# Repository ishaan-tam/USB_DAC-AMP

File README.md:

# Pocket USB DAC Headphone Amp

# USB DAC + Baxandall Tone Control Headphone Amp  
**Checklist / Build Plan**

make sure that resistors are thin film, thich film resistors can introduce distortion
Chose electrolytic caps in the signal path as long as they are large enough, if chosing ceramic (sepecially in the signal path) chose type cog, otehrwise most ceramic caps will have piezoelectric effects and will introduce distortion 
bypass caps can be pretty much any type

For voltage ratings, useually go with double of what the expected DC voltage is
---

## Phase 0 — Lock the architecture
- [ ] Use **Phil’s USB headphone amplifier** as the base design
  - [ ] USB-C power + data
  - [ ] USB audio codec (PCM290x family)
  - [ ] DAC output buffer / reconstruction filter
  - [ ] Volume control stage
  - [ ] Output/current-drive stage to headphone jack
- [ ] Insert **TI Baxandall bass/treble tone control** as a line-level block
  - [ ] Signal flow:  
    **Phil DAC buffer → TI Baxandall tone → Phil volume → Phil output stage**
- [ ] Decide on **single master volume**
  - [ ] Use Phil’s volume control only
  - [ ] Bypass TI’s R1/R2 volume pots

---

## Phase 1 — KiCad schematic integration
- [ ] Create a **combined KiCad schematic**
  - [ ] Start from Phil’s schematic as the backbone
  - [ ] Add TI Baxandall tone block between Phil buffer output and Phil volume input
  - [ ] Keep TI input buffers initially (lower risk)
- [ ] **Bypass TI R1/R2 (volume pots)**
  - [ ] Remove R1/R2 from the TI tone schematic
  - [ ] Feed TI input buffer directly from the coupling cap
  - [ ] Add a DC bias path so the node does not float
  - [ ] (Optional) Add footprints / jumpers to re-enable pots if needed
- [ ] **Resolve virtual ground vs real ground**
  - [ ] Identify Phil’s analog reference / bias node (half-rail if single-supply)
  - [ ] Tie all TI “mid” nodes to Phil’s analog reference
  - [ ] Do NOT generate a separate TI virtual ground if Phil already provides one
- [ ] Perform a **sanity check**
  - [ ] Verify signal levels between stages
  - [ ] Ensure tone boost will not clip internal op-amps
  - [ ] Ensure compatibility with Phil’s volume stage input impedance

---

## Phase 2 — BOM & sourcing
- [ ] Create a **BOM from the combined schematic**
  - [ ] ICs (codec, op-amps, regulators)
  - [ ] Precision resistors where required
  - [ ] Capacitors (type + voltage rating)
  - [ ] Dual-gang pots for bass/treble
  - [ ] USB-C connector, headphone jack
  - [ ] Protection parts (ESD diodes, fuses, ferrites)
- [ ] Align BOM with **JLCPCB / LCSC availability**
  - [ ] Decide which ICs are hand-soldered
  - [ ] Mark which passives are PCBA-assembled
- [ ] Order parts
  - [ ] Order extras for iteration (pots, op-amps, passives)

---

## Phase 3 — Build & test
- [ ] Bring-up in stages
  - [ ] Test Phil’s base circuit (USB enumeration + clean audio)
  - [ ] Enable TI Baxandall tone block
  - [ ] Verify flat response at center
  - [ ] Verify bass/treble behavior
- [ ] Full system test
  - [ ] Verify volume control behavior
  - [ ] Test with headphones
  - [ ] Listen for noise, clipping, oscillation

---

## Phase 4 — Rev A refinement
- [ ] Adjust Baxandall network for **subtle** tone range if needed
- [ ] Improve decoupling/layout if noise or instability appears
- [ ] Finalize schematic and prepare for PCB layout / PCBA

A compact, USB-powered headphone amplifier built around a **class-compliant USB audio codec**, with an **analog signal path**, **physical volume control**, and room to add **Baxandall bass/treble tone shaping** in later revisions.

This project prioritizes:
- **Fun, hands-on analog audio**
- **Simple, driverless USB DAC operation**
- **Incremental development** (breadboard → PCB Rev A → Rev B tone control)

Not meant to be “audiophile-perfect,” but absolutely meant to be **good enough that I actually want to use it**.

---

## Project Status

- **Current phase:** Rev 0 — Breadboard prototype
- **Goal of Rev 0:**  
  - USB device enumerates as an audio output  
  - Audio plays cleanly through headphones  
  - Volume control works  
- **Future phases:**  
  - Rev A PCB (compact, USB-C, integrated headphone stage)  
  - Rev B (add Baxandall bass/treble tone control)

---

## High-Level Architecture

USB-C
│
├─ USB 2.0 D+/D−
│
PCM2906C USB Audio Codec
│
├─ DAC L/R (line-level)
│
Buffer + Reconstruction Filter
│
(Rev B) Baxandall Tone Control (Bass / Treble)
│
Volume Control
│
Headphone Output Stage
│
3.5 mm Headphone Jack

---

## Key Design Decisions

### USB Audio Codec
- **TI PCM2906C**
  - USB Audio Class 1 (driverless)
  - Plug-and-play on **Windows, macOS, Linux**
  - Likely works on **USB-C iPhones** (with power constraints)
  - Chosen over older PCM2900 due to **availability / active status**

S/PDIF pins are **not used** in this project.

---

### Power Strategy
- **Rev 0 (breadboard):**  
  - USB 5 V only  
  - No boost converter  
- **Rev A (PCB):**  
  - USB 5 V → boost → clean analog rail (12–15 V)  
  - Boost is for **headroom**, not “audio amplification”

---

### Analog Audio Philosophy
- Keep the **DAC isolated** from headphone loads
- Use **buffers** and **volume control** before the output stage
- Tone control is **optional and playful**, not surgical EQ
- If “serious EQ” is needed → do it digitally in software

---

### Tone Control Plan
- **Baxandall bass/treble** (2 knobs)
  - Musical, forgiving
  - Simple, stable, well-understood
- Will be added in **Rev B**
- Rev A PCB should reserve insertion points for it

---

## Breadboard Prototype (Rev 0)

### What Rev 0 Includes
- PCM2906C wired per TI **Typical Application Circuit**
- 12 MHz crystal + required decoupling
- USB-C input (USB 2.0 only)
- Line-level L/R output
- External headphone amp module **or** simple buffer + volume pot
- Goal: **“I hear sound and can control volume”**

### What Rev 0 Intentionally Avoids
- Boost converters
- Parallel op-amps
- Tone controls
- EMI optimization
- Fancy layouts

Rev 0 is about **function, not polish**.

---

## Headphone Output (Rev 0 Approach)

For breadboarding, the headphone stage is intentionally simplified:

### Options
1. **External headphone amp module**
   - Accepts line-level L/R
   - Powered from 5 V
   - Drives headphones safely
2. **DIY buffer + volume + output stage**
   - Unity-gain buffer
   - Passive volume pot
   - Headphone-capable driver

Modules are preferred for Rev 0 to avoid stability issues on a breadboard.

---

## Compatibility Expectations

- **Windows:** ✅ Plug-and-play
- **macOS / Linux:** ✅ Plug-and-play
- **USB-C iPhone:** ⚠️ Likely works, power-dependent
- **Lightning iPhone:** ⚠️ Requires camera adapter

---

## Repository Structure

pocket-usb-dac-amp/
├─ README.md
├─ docs/
│ ├─ requirements.md
│ ├─ architecture.md
│ ├─ bringup-notes.md
│ └─ images/
├─ hardware/
│ ├─ rev0_breadboard/
│ │ ├─ wiring/
│ │ └─ bom/
│ │ └─ bom_rev0.xlsx
│ ├─ revA_pcb/
│ │ ├─ kicad/
│ │ ├─ outputs/
│ │ └─ bom/
│ └─ revB_tonecontrol/
├─ tools/
│ └─ bom/
└─ CHANGELOG.md

---

## BOM Management

- BOMs are maintained in **Excel**
- Each revision has its own BOM:
  - `bom_rev0.xlsx`
  - `bom_revA.xlsx`
- BOM includes:
  - Manufacturer + MPN
  - Supplier + SKU
  - Unit cost
  - Alternates
  - Notes (DNP, experimental, etc.)

KiCad-exported CSVs are treated as **derived artifacts**, not the source of truth.

---

## Development Philosophy

- Build **one working version at a time**
- Breadboard first, PCB later
- Prefer **known-good reference circuits**
- Avoid “clever” designs that increase debug time
- Leave room for iteration and learning

---

## Non-Goals (Important)

- Not chasing ultra-low THD numbers
- Not competing with commercial DACs
- Not building a DSP playground
- Not optimizing for mass production

This is a **learning + enjoyment project**, not a product launch.

---

## Next Immediate Steps

1. Finish Rev 0 breadboard wiring
2. Confirm USB enumeration + audio playback
3. Document bring-up issues and fixes
4. Decide:
   - integrated output stage vs module
5. Begin Rev A schematic capture

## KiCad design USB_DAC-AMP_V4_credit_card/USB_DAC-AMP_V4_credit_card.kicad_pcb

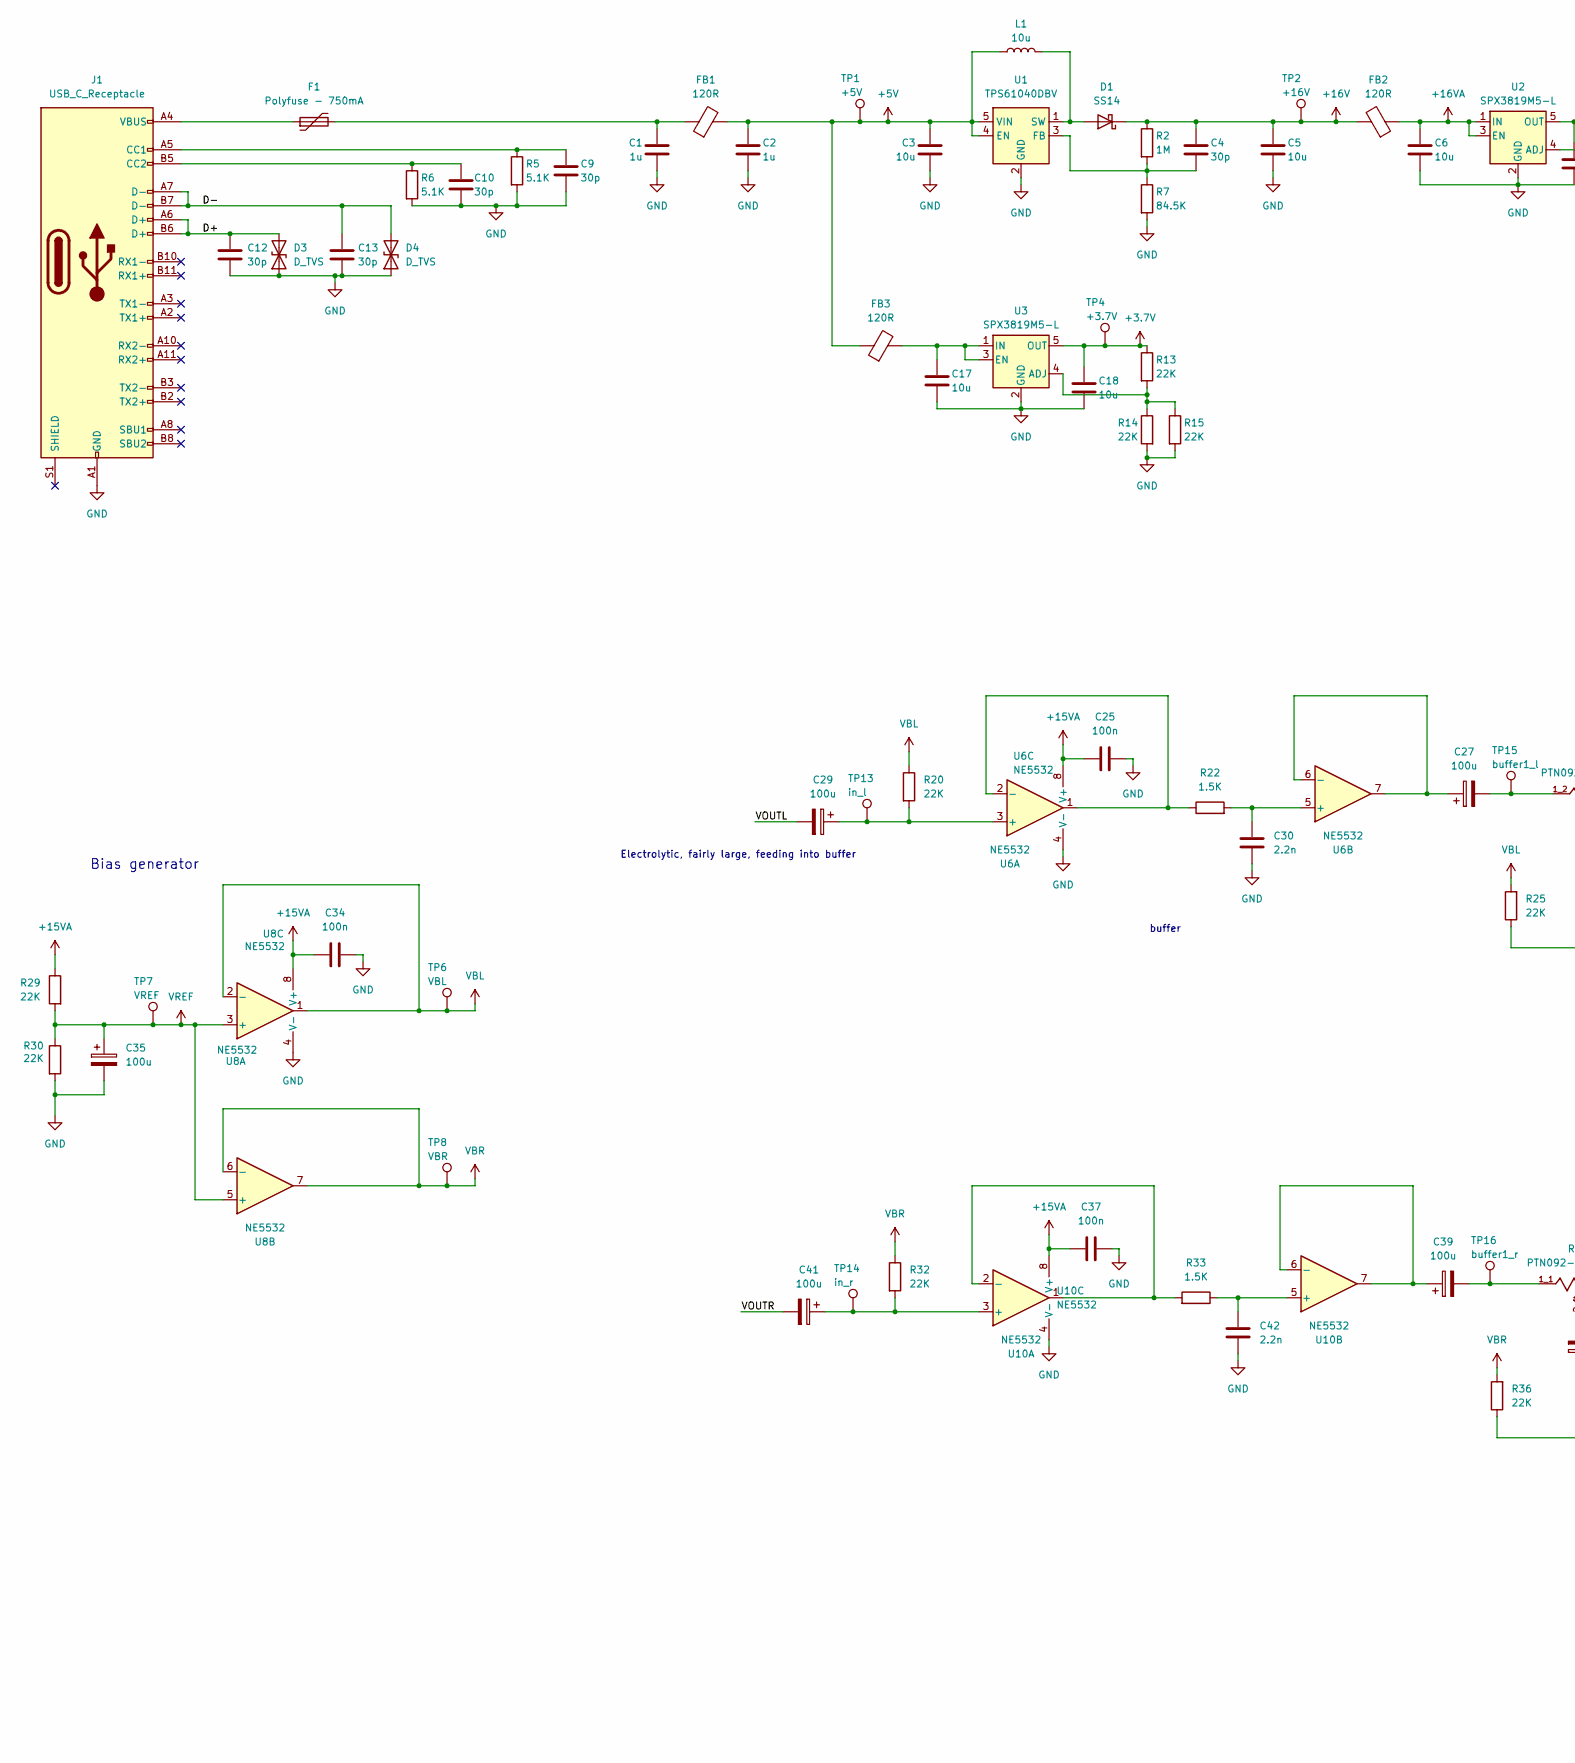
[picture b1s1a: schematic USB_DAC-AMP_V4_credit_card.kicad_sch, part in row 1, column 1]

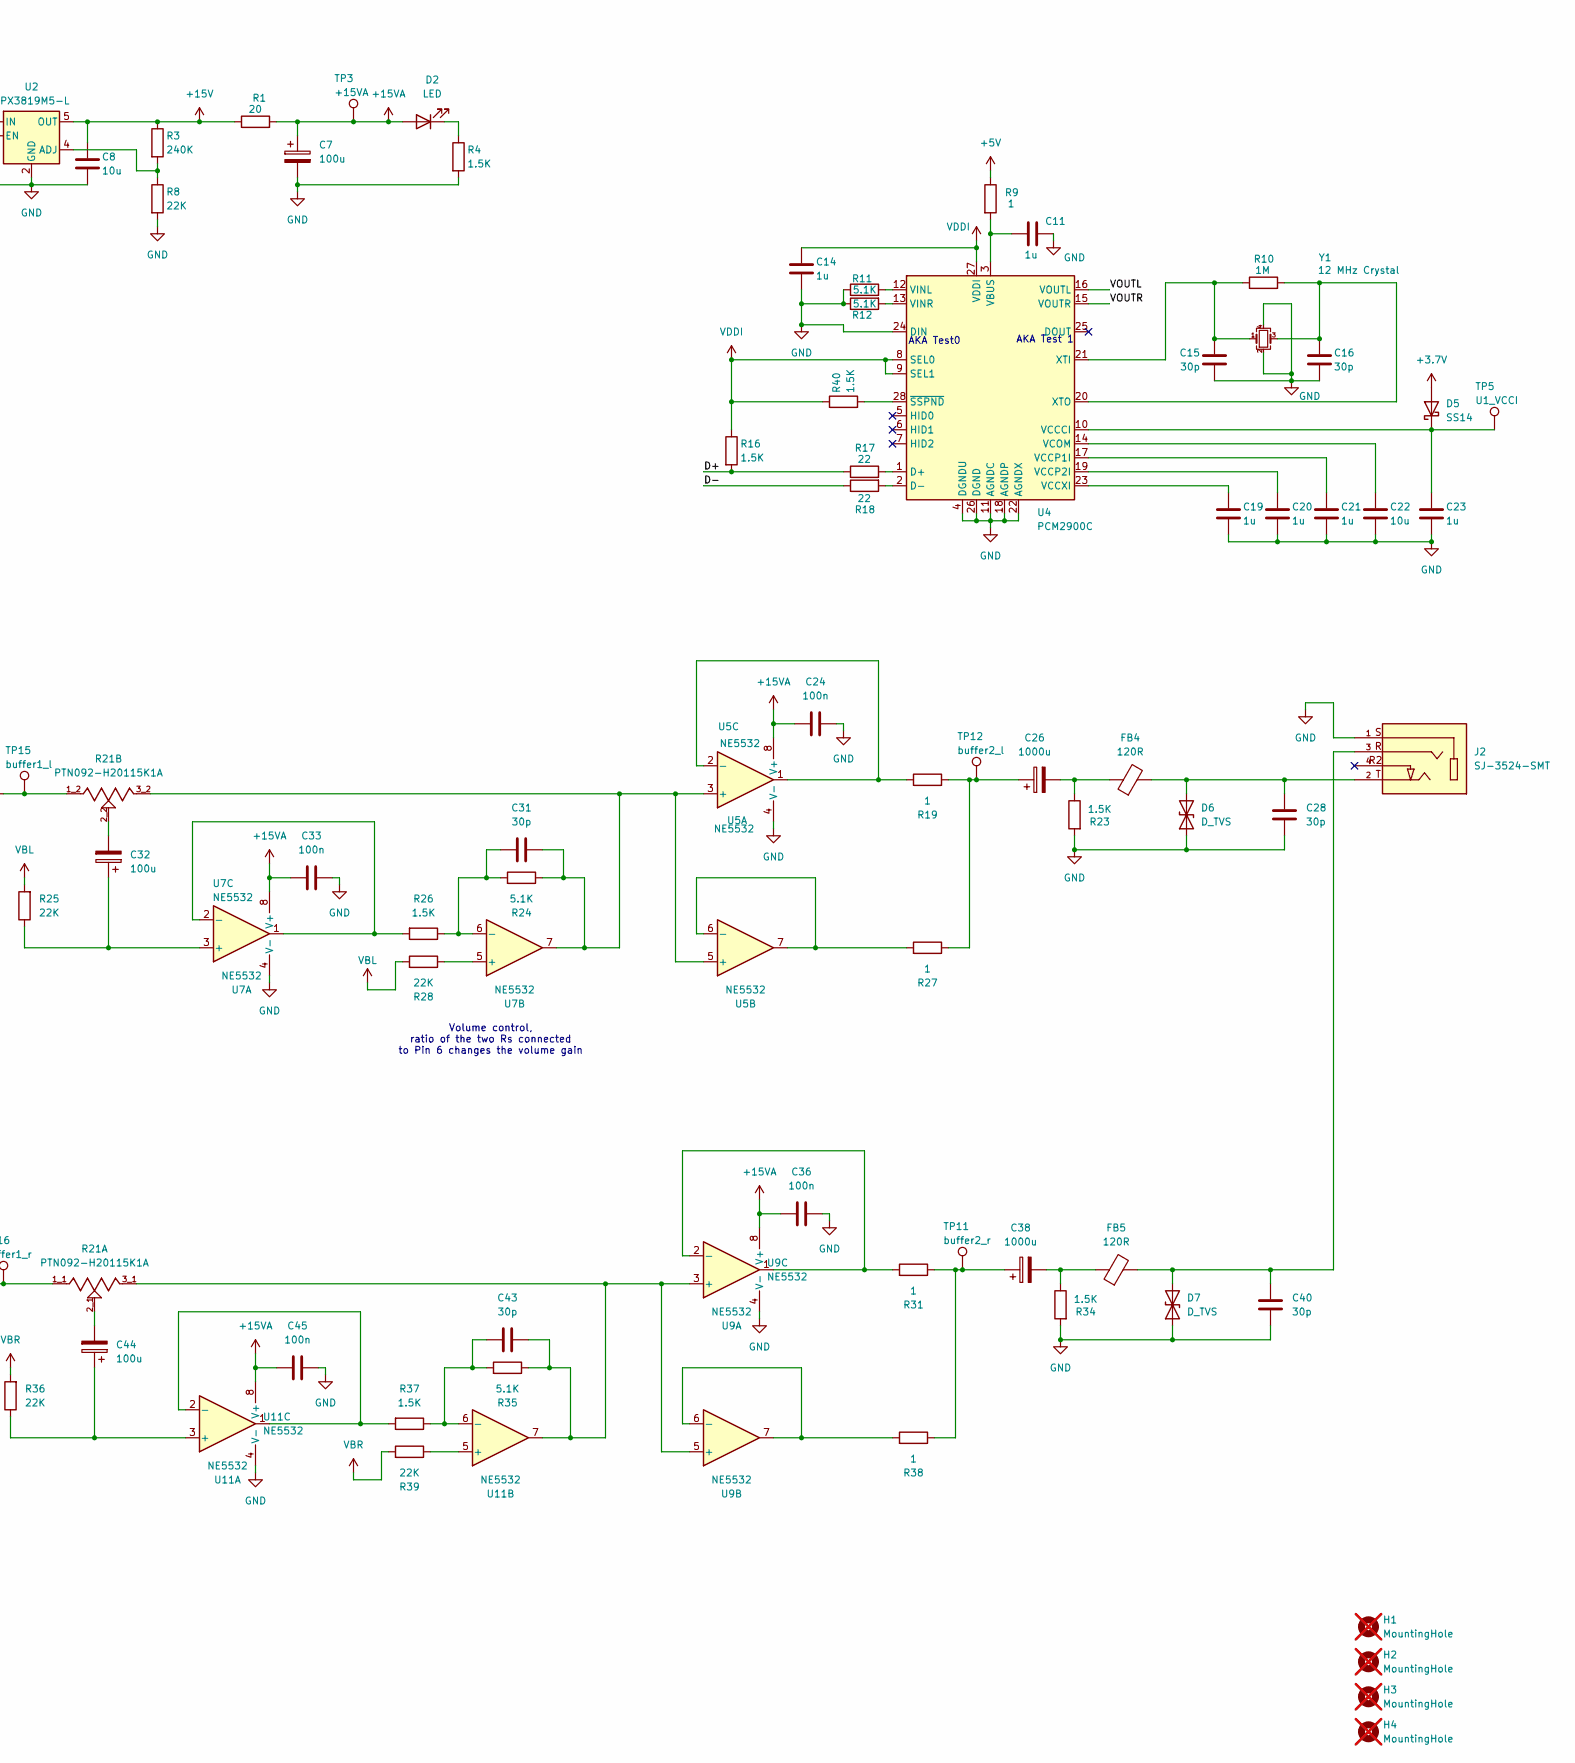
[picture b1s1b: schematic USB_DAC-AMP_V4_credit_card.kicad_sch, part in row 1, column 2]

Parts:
C1, C2, C11, C14, C19, C20, C21, C23: 1u; C_0603_1608Metric; LCSC C1592
C3, C5, C6, C8, C17, C18, C22: 10u; C_0603_1608Metric; LCSC C1035
C4, C9, C10, C12, C13, C15, C16, C28, C31, C40, C43: 30p; C_0603_1608Metric; LCSC C1658
C7, C27, C29, C32, C35, C39, C41, C44: 100u; CP_Elec_6.3x7.7; LCSC C3339
C24, C25, C33, C34, C36, C37, C45: 100n; C_0603_1608Metric; LCSC C1590
C26, C38: 1000u; CP_Elec_10x10.5; LCSC C3359
C30, C42: 2.2n; C_0603_1608Metric; LCSC C1028
D1, D5: SS14; D_SMA; LCSC C2480
D2: LED; LED_0603_1608Metric; LCSC C84265
D3, D4, D6, D7: D_TVS; D_0603_1608Metric; LCSC C316055
F1: Polyfuse - 750mA; Fuse_0603_1608Metric; LCSC C20787
FB1, FB2, FB3, FB4, FB5: 120R; R_0603_1608Metric; LCSC C12391
H1, H2, H3, H4: MountingHole; MountingHole_3.5mm; not fitted
J1: USB_C_Receptacle; USB_C_Receptacle_GCT_USB4105-xx-A_16P_TopMnt_Horizontal; LCSC C5184243
J2: SJ-3524-SMT; PARTREV 1.03; DigiKey_Part_Number CP-3524SJCT-ND
L1: 10u; L_0805_2012Metric; LCSC C223269
R1: 20; R_0603_1608Metric; LCSC C136969
R2, R10: 1M; R_0603_1608Metric; LCSC C326730
R3: 240K; R_0603_1608Metric; LCSC C217899
R4, R16, R22, R23, R26, R33, R34, R37, R40: 1.5K; R_0603_1608Metric; LCSC C193681
R5, R6, R11, R12, R24, R35: 5.1K; R_0603_1608Metric; LCSC C122969
R7: 84.5K; R_0603_1608Metric; LCSC C705797
R8, R13, R14, R15, R20, R25, R28, R29, R30, R32, R36, R39: 22K; R_0603_1608Metric; LCSC C217885
R9, R19, R27, R31, R38: 1; R_0603_1608Metric; LCSC C412388
R17, R18: 22; R_0603_1608Metric; LCSC C217888
R21: PTN092-H20115K1A; TRIM_PTN092-H20115K1A; PARTREV 1.01; DigiKey_Part_Number 2223-PTN092-H20115K1A-ND
TP1: +5V; TestPoint_Pad_1.0x1.0mm
TP2: +16V; TestPoint_Pad_1.0x1.0mm
TP3: +15VA; TestPoint_Pad_1.0x1.0mm
TP4: +3.7V; TestPoint_Pad_1.0x1.0mm
TP5: U1_VCCI; TestPoint_Pad_1.0x1.0mm
TP6: VBL; TestPoint_Pad_1.0x1.0mm
TP7: VREF; TestPoint_Pad_1.0x1.0mm
TP8: VBR; TestPoint_Pad_1.0x1.0mm
TP11: buffer2_r; TestPoint_Pad_1.0x1.0mm
TP12: buffer2_l; TestPoint_Pad_1.0x1.0mm
TP13: in_l; TestPoint_Pad_1.0x1.0mm
TP14: in_r; TestPoint_Pad_1.0x1.0mm
TP15: buffer1_l; TestPoint_Pad_1.0x1.0mm
TP16: buffer1_r; TestPoint_Pad_1.0x1.0mm
U1: TPS61040DBV; SOT-23-5; LCSC C7722
U2, U3: SPX3819M5-L; SOT-23-5; LCSC C9056
U4: PCM2900C; SSOP-28_5.3x10.2mm_P0.65mm; LCSC C180425
U5, U6, U7, U8, U9, U10, U11: NE5532; SOIC-8_3.9x4.9mm_P1.27mm; LCSC C7426
Y1: 12 MHz Crystal; Crystal_SMD_3225-4Pin_3.2x2.5mm; LCSC C9002

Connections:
+3.7V: C18.1, D5.2 (A), R13.1, TP4.1, U3.5 (OUT)
+5V: C2.1, C3.1, FB1.2, FB3.1, L1.1, R9.1, TP1.1, U1.4 (EN), U1.5 (VIN)
+15V: C8.1, R1.1, R3.1, U2.5 (OUT)
+15VA: C7.1, C24.1, C25.1, C33.1, C34.1, C36.1, C37.1, C45.1, D2.2 (A), R1.2, R29.1, TP3.1, U5.8 (V+), U6.8 (V+), U7.8 (V+), U8.8 (V+), U9.8 (V+), U10.8 (V+), U11.8 (V+)
+16V: C4.1, C5.1, D1.1 (K), FB2.2, R2.1, TP2.1
+16VA: C6.1, FB2.1, U2.1 (IN), U2.3 (EN)
/D+: C12.1, D3.2 (A2), J1.A6 (D+), J1.B6 (D+), R16.2, R17.1
/D-: C13.1, D4.2 (A2), J1.A7 (D-), J1.B7 (D-), R18.1
/VOUTL: C29.2, U4.16 (VOUTL)
/VOUTR: C41.2, U4.15 (VOUTR)
GND: C1.2, C2.2, C3.2, C5.2, C6.2, C7.2, C8.2, C9.2, C10.2, C11.2, C12.2, C13.2, C14.2, C15.2, C16.2, C17.2, C18.2, C19.2, C20.2, C21.2, C22.2, C23.2, C24.2, C25.2, C28.1, C30.1, C33.2, C34.2, C35.2, C36.2, C37.2, C40.1, C42.1, C45.2, D3.1 (A1), D4.1 (A1), D6.1 (A1), D7.1 (A1), J1.A1 (GND), J1.A12 (GND), J1.B1 (GND), J1.B12 (GND), J2.1, R4.2, R5.2, R6.2, R7.2, R8.2, R11.1, R12.1, R14.2, R15.2, R23.2, R30.2, R34.2, U1.2 (GND), U2.2 (GND), U3.2 (GND), U4.4 (DGNDU), U4.11 (AGNDC), U4.18 (AGNDP), U4.22 (AGNDX), U4.24 (DIN), U4.26 (DGND), U5.4 (V-), U6.4 (V-), U7.4 (V-), U8.4 (V-), U9.4 (V-), U10.4 (V-), U11.4 (V-), Y1.2, Y1.4
unnamed: C1.1, F1.2, FB1.1
unnamed: C26.1, R19.2, R27.1, TP12.1
unnamed: C26.2, FB4.1, R23.1
unnamed: C27.2, R21.1_2, TP15.1
unnamed: C32.2, R21.2_2
unnamed: C38.1, R31.1, R38.1, TP11.1
unnamed: C38.2, FB5.1, R34.1
unnamed: C39.2, R21.1_1, TP16.1
unnamed: C44.2, R21.2_1
unnamed: D1.2 (A), L1.2, U1.1 (SW)
unnamed: D2.1 (K), R4.1
unnamed: C23.1, D5.1 (K), TP5.1, U4.10 (VCCCI)
unnamed: C28.2, D6.2 (A2), FB4.2, J2.2
unnamed: C40.2, D7.2 (A2), FB5.2, J2.3
unnamed: F1.1, J1.A4 (VBUS), J1.A9 (VBUS), J1.B4 (VBUS), J1.B9 (VBUS)
unnamed: C9.1, J1.A5 (CC1), R5.1
unnamed: C10.1, J1.B5 (CC2), R6.1
unnamed: C4.2, R2.2, R7.1, U1.3 (FB)
unnamed: R3.2, R8.1, U2.4 (ADJ)
unnamed: R13.2, R14.1, R15.1, U3.4 (ADJ)
unnamed: C17.1, FB3.2, U3.1 (IN), U3.3 (EN)
unnamed: R17.2, U4.1 (D+)
unnamed: R18.2, U4.2 (D-)
unnamed: C11.1, R9.2, U4.3 (VBUS)
unnamed: C21.1, U4.17 (VCCP1I)
unnamed: C20.1, U4.19 (VCCP2I)
unnamed: C19.1, U4.23 (VCCXI)
unnamed: C22.1, U4.14 (VCOM)
unnamed: R11.2, U4.12 (VINL)
unnamed: R12.2, U4.13 (VINR)
unnamed: C15.1, R10.1, U4.21 (XTI), Y1.1
unnamed: C16.1, R10.2, U4.20 (XTO), Y1.3
unnamed: R40.2, U4.28 (~SSPND)
unnamed: C31.2, R21.3_2, R24.1, U5.3 (+), U5.5 (+), U7.7
unnamed: R19.1, U5.1, U5.2 (-)
unnamed: R27.2, U5.6 (-), U5.7
unnamed: C29.1, R20.2, TP13.1, U6.3 (+)
unnamed: R22.1, U6.1, U6.2 (-)
unnamed: C30.2, R22.2, U6.5 (+)
unnamed: C27.1, U6.6 (-), U6.7
unnamed: C32.1, R25.1, U7.3 (+)
unnamed: R26.2, U7.1, U7.2 (-)
unnamed: R28.1, U7.5 (+)
unnamed: C31.1, R24.2, R26.1, U7.6 (-)
unnamed: C43.2, R21.3_1, R35.1, U9.3 (+), U9.5 (+), U11.7
unnamed: R31.2, U9.1, U9.2 (-)
unnamed: R38.2, U9.6 (-), U9.7
unnamed: C41.1, R32.2, TP14.1, U10.3 (+)
unnamed: R33.2, U10.1, U10.2 (-)
unnamed: C42.2, R33.1, U10.5 (+)
unnamed: C39.1, U10.6 (-), U10.7
unnamed: C44.1, R36.1, U11.3 (+)
unnamed: R37.2, U11.1, U11.2 (-)
unnamed: R39.1, U11.5 (+)
unnamed: C43.1, R35.2, R37.1, U11.6 (-)
VBL: R20.1, R25.2, R28.2, TP6.1, U8.1, U8.2 (-)
VBR: R32.1, R36.2, R39.2, TP8.1, U8.6 (-), U8.7
VDDI: C14.1, R16.1, R40.1, U4.8 (SEL0), U4.9 (SEL1), U4.27 (VDDI)
VREF: C35.1, R29.2, R30.1, TP7.1, U8.3 (+), U8.5 (+)

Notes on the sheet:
AKA Test 1
buffer
Bias generator
Electrolytic, fairly large, feeding into buffer
AKA Test0
Volume control, ratio of the two Rs connected to Pin 6 changes the volume gain

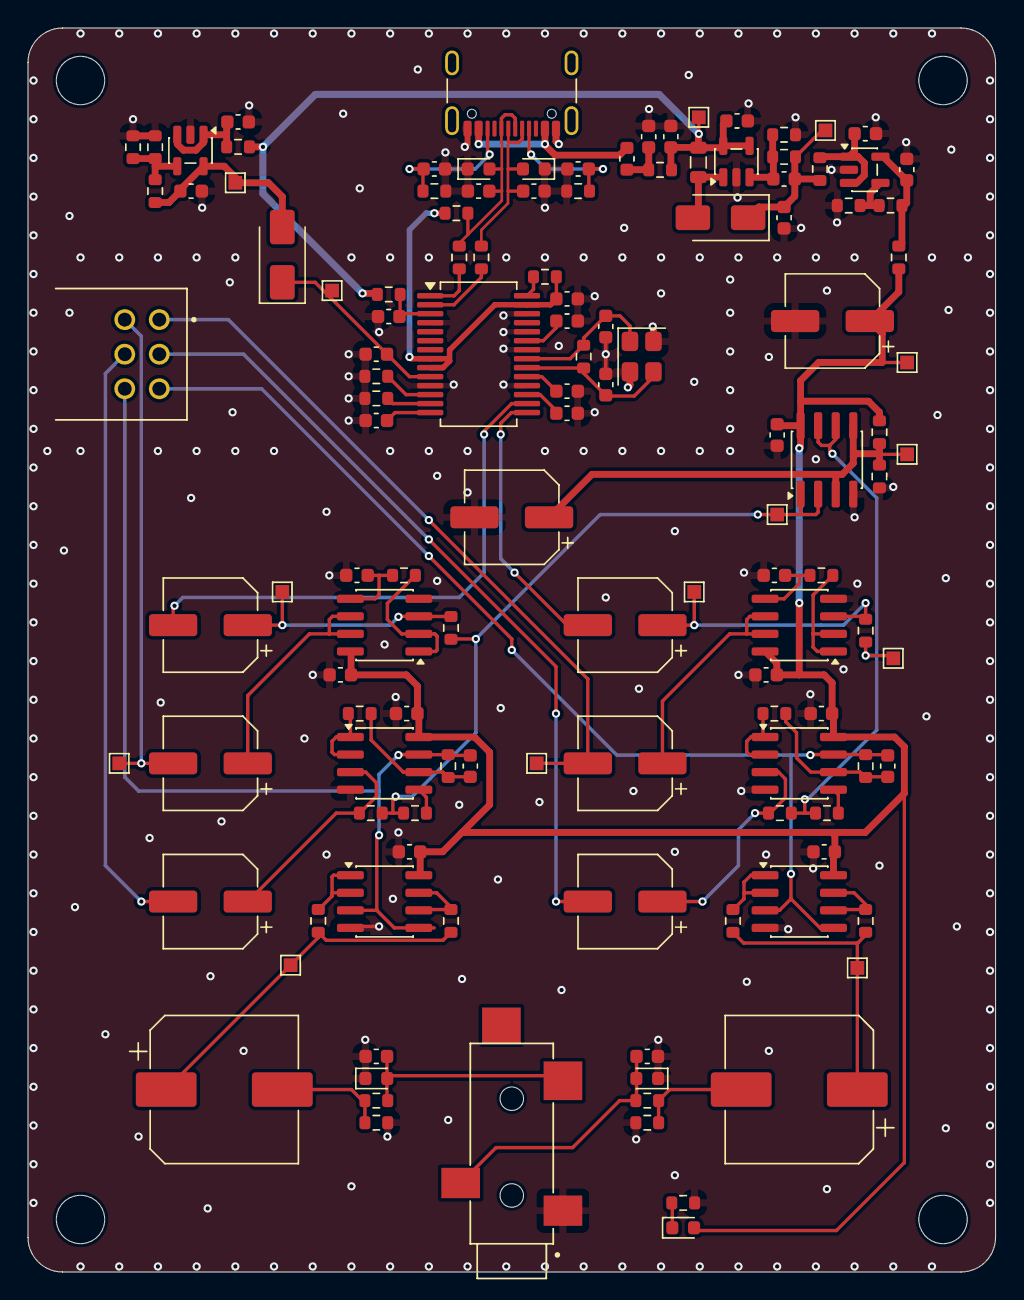
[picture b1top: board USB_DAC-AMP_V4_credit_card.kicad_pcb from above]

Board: 4 copper layers, 70.0 x 90.0 mm, 131 parts (0 on the bottom side), 70 nets.

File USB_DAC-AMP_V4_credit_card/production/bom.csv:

Designator,Footprint,Quantity,Value,LCSC Part #
"C1, C11, C14, C19, C2, C20, C21, C23",0603,8,1u,C1592
"C10, C12, C13, C15, C16, C28, C31, C4, C40, C43, C9",0603,11,30p, C1658
"C17, C18, C22, C3, C5, C6, C8",0603,7,10u,C1035
"C24, C25, C33, C34, C36, C37, C45",0603,7,100n,C1590
"C26, C38",CP_Elec_10x10.5,2,1000u,C3359
"C27, C29, C32, C35, C39, C41, C44, C7",CP_Elec_6.3x7.7,8,100u,C3339
"C30, C42",0603,2,2.2n,C1028
"D1, D5",D_SMA,2,SS14,C2480
D2,0603,1,LED,C84265
"D3, D4, D6, D7",0603,4,D_TVS,C316055
F1,0603,1,Polyfuse - 750mA,C20787
"FB1, FB2, FB3, FB4, FB5",0603,5,120R,C12391
J1,USB_C_Receptacle_GCT_USB4105-xx-A_16P_TopMnt_Horizontal,1,USB_C_Receptacle,C5184243
J2,SJ-3524-SMT,1,SJ-3524-SMT,
L1,0805,1,10u,C223269
R1,0603,1,20,C136969
"R10, R2",0603,2,1M,C326730
"R11, R12, R24, R35, R5, R6",0603,6,5.1K,C122969
"R13, R14, R15, R20, R25, R28, R29, R30, R32, R36, R39, R8",0603,12,22K,C217885
"R16, R22, R23, R26, R33, R34, R37, R4, R40",0603,9,1.5K,C193681
"R17, R18",0603,2,22,C217888
"R19, R27, R31, R38, R9",0603,5,1,C412388
R21,TRIM_PTN092-H20115K1A,1,PTN092-H20115K1A,
R3,0603,1,240K,C217899
R7,0603,1,84.5K,C705797
TP1,TestPoint_Pad_1.0x1.0mm,1,+5V,
TP11,TestPoint_Pad_1.0x1.0mm,1,buffer2_r,
TP12,TestPoint_Pad_1.0x1.0mm,1,buffer2_l,
TP13,TestPoint_Pad_1.0x1.0mm,1,in_l,
TP14,TestPoint_Pad_1.0x1.0mm,1,in_r,
TP15,TestPoint_Pad_1.0x1.0mm,1,buffer1_l,
TP16,TestPoint_Pad_1.0x1.0mm,1,buffer1_r,
TP2,TestPoint_Pad_1.0x1.0mm,1,+16V,
TP3,TestPoint_Pad_1.0x1.0mm,1,+15VA,
TP4,TestPoint_Pad_1.0x1.0mm,1,+3.7V,
TP5,TestPoint_Pad_1.0x1.0mm,1,U1_VCCI,
TP6,TestPoint_Pad_1.0x1.0mm,1,VBL,
TP7,TestPoint_Pad_1.0x1.0mm,1,VREF,
TP8,TestPoint_Pad_1.0x1.0mm,1,VBR,
U1,SOT-23-5,1,TPS61040DBV,C7722
"U10, U11, U5, U6, U7, U8, U9",SOIC-8_3.9x4.9mm_P1.27mm,7,NE5532,C7426
"U2, U3",SOT-23-5,2,SPX3819M5-L,C9056
U4,SSOP-28_5.3x10.2mm_P0.65mm,1,PCM2900C,C180425
Y1,Crystal_SMD_3225-4Pin_3.2x2.5mm,1,12 MHz Crystal,C9002
